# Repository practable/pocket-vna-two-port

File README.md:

# pocket-vna-two-port

A golang-based web service for the pocketvna.com](https://pocketvna.com/) vector network analyser, with an automated two-port calibration facility provided by additional RF hardware, for use with the open-source [practable.io](https://practable.io] remote lab ecosystem. The user interface is similar to [this](https://github.com/dpreid/pidui), although not yet publically released by the developer (coming soon!)

Status: Prototype has passed measurement quality check, and firmware has been updated to two-ports.

## API

Note that the optional "id" parameter does not affect the command itself, and is provided to help associate replies with the commands that produced them (in case responses come out of order)

### Reasonable range 

```
{"id":"rr","cmd":"rr"}
```
Response:
```
{"id":"rr","t":0,"cmd":"rr","range":{"start":500000,"end":4000000000}}
```

### Calibration

To Perform a full 2-port calibration issue a command like this:

```
{"id":"rcal","t":0,"cmd":"rc","range":{"start":1000000,"end":4000000000},"size":501,"islog":false,"avg":1}
```

501 points is quite slow, so for quick checking functionality, try fewer points.
```
{"id":"rcal","t":0,"cmd":"rc","range":{"start":1000000,"end":4000000000},"size":5,"islog":false,"avg":1}
```

 The `range`, `size`, `isLog` and `avg` are the same as before. This example uses the largest scan size possible (501 points)

### Measurement

These are all the measurements that can be taken (as before, they use the size, and range parameters from the cal):

```
{"id":"short","t":0,"cmd":"crq","what":"short","avg":1,"sparam":{"s11":true,"s12":true, "s21":true,"s22":true}}
{"id":"open","t":0,"cmd":"crq","what":"open","avg":1,"sparam":{"s11":true,"s12":true,"s21":true,"s22":true}}
{"id":"load","t":0,"cmd":"crq","what":"load","avg":1,"sparam":{"s11":true,"s12":true,"s21":true,"s22":true}}
{"id":"thru","t":0,"cmd":"crq","what":"thru","avg":1,"sparam":{"s11":true,"s12":true,"s21":true,"s22":true}}
{"id":"dut1","t":0,"cmd":"crq","what":"dut1","avg":1,"sparam":{"s11":true,"s12":true,"s21":true,"s22":true}}
{"id":"dut2","t":0,"cmd":"crq","what":"dut2","avg":1,"sparam":{"s11":true,"s12":true,"s21":true,"s22":true}}
{"id":"dut3","t":0,"cmd":"crq","what":"dut3","avg":1,"sparam":{"s11":true,"s12":true,"s21":true,"s22":true}}
{"id":"dut4","t":0,"cmd":"crq","what":"dut4","avg":1,"sparam":{"s11":true,"s12":true,"s21":true,"s22":true}} 
```

### Step wise calibration

New feature added to support students learning about the cal process

SC Command (Setup cal, sets the frequency range, number of points, distribution type, and averaging count)
`{"cmd":"sc","range":{"start":1000000,"end":4000000000},"size":20,"islog":false,"avg":1}`

SC Response
```
{"message":"ok","Command":{"id":"","t":0,"cmd":"sc","range":{"start":1000000,"end":4000000000},"size":20,"islog":false,"avg":1,"sparam":{"s11":false,"s12":false,"s21":false,"s22":false},"result":null,"what":"thru"}}
```

MC Short Command:
`{"cmd":"mc","what":"short"}`

MC Short Response (has no data):
```
{"message":"ok","Command":{"id":"","t":0,"cmd":"mc","range":{"start":0,"end":0},"size":0,"islog":false,"avg":0,"sparam":{"s11":false,"s12":false,"s21":false,"s22":false},"result":null,"what":"short"}}
```

MC Open Command:
`{"cmd":"mc","what":"open"}`

MC Open Response (has no data):
```
{"message":"ok","Command":{"id":"","t":0,"cmd":"mc","range":{"start":0,"end":0},"size":0,"islog":false,"avg":0,"sparam":{"s11":false,"s12":false,"s21":false,"s22":false},"result":null,"what":"open"}}
```

MC Load Command:
`{"cmd":"mc","what":"load"}`

MC Load Response (has no data):
```
{"message":"ok","Command":{"id":"","t":0,"cmd":"mc","range":{"start":0,"end":0},"size":0,"islog":false,"avg":0,"sparam":{"s11":false,"s12":false,"s21":false,"s22":false},"result":null,"what":"load"}}
```

MC Thru Command:

`{"cmd":"mc","what":"thru"}`

MC Thru Response (has no data):

```
{"message":"ok","Command":{"id":"","t":0,"cmd":"mc","range":{"start":0,"end":0},"size":0,"islog":false,"avg":0,"sparam":{"s11":false,"s12":false,"s21":false,"s22":false},"result":null,"what":"thru"}}
```

CC Command (cal confirm):

`{"cmd":"cc"}`

CC Command (has data, "what" indicates this is data for the thru with cal applied)
```
{"id":"","t":0,"cmd":"cc","range":{"start":0,"end":0},"size":0,"islog":false,"avg":0,"sparam":{"s11":false,"s12":false,"s21":false,"s22":false},"result":[{"s11":{"real":6.798285684431499e-16,"imag":2.4445757591977986e-15},"s12":{"real":1.0000000000000038,"imag":3.961372257700955e-15},"s21":{"real":0.9999999999999997,"imag":-2.5403542658420376e-15},"s22":{"real":-1.3100837207899224e-16,"imag":1.006857580582699e-15},"freq":1000000},{"s11":{"real":-5.4796192872464335e-18,"imag":3.681361022427108e-16},"s12":{"real":0.9999999999999998,"imag":1.291216167493111e-16},"s21":{"real":0.9999999999999998,"imag":1.0329729339944889e-16},"s22":{"real":-5.483483876630498e-16,"imag":2.274972688902102e-16},"freq":211473684},{"s11":{"real":4.935662660074536e-16,"imag":-7.96132869667085e-17},"s12":{"real":1.0000000000000002,"imag":9.417544964280893e-18},"s21":{"real":1,"imag":3.3389477600632256e-17},"s22":{"real":-5.493611090297354e-17,"imag":2.7110250401774997e-17},"freq":421947368},{"s11":{"real":-3.7997788415861466e-16,"imag":-5.874815142871674e-16},"s12":{"real":0.9999999999999998,"imag":-1.3589387524604561e-17},"s21":{"real":1,"imag":1.358938752460456e-16},"s22":{"real":2.7701351888980784e-16,"imag":2.4761558453947516e-16},"freq":632421052},{"s11":{"real":-1.770339245638541e-16,"imag":1.9778244425109326e-16},"s12":{"real":1,"imag":-8.300789127383292e-17},"s21":{"real":1,"imag":-1.3834648545638821e-17},"s22":{"real":1.8971165707760076e-16,"imag":2.4057070110192795e-16},"freq":842894736},{"s11":{"real":-4.2721621505142654e-16,"imag":-3.6944203527273236e-16},"s12":{"real":1.0000000000000002,"imag":1.0316557900882054e-16},"s21":{"real":1,"imag":2.3212255276984624e-16},"s22":{"real":1.4673180020770904e-16,"imag":-7.563249442097559e-17},"freq":1053368421},{"s11":{"real":-7.434581424175234e-17,"imag":-1.9738283167151276e-16},"s12":{"real":1.0000000000000007,"imag":2.653377447265651e-16},"s21":{"real":1,"imag":1.3668914122277596e-16},"s22":{"real":-2.3401087672749595e-16,"imag":1.0842732839585657e-15},"freq":1263842105},{"s11":{"real":3.6225925572304583e-16,"imag":-6.553331226630913e-16},"s12":{"real":1.0000000000000002,"imag":-7.697793525240971e-18},"s21":{"real":1,"imag":-2.232360122319882e-16},"s22":{"real":-1.664758573382055e-16,"imag":4.426697324102885e-16},"freq":1474315789},{"s11":{"real":-2.1111596138986894e-16,"imag":-3.374000478864848e-16},"s12":{"real":0.9999999999999998,"imag":2.500148396700068e-16},"s21":{"real":0.9999999999999997,"imag":1.388971331500038e-16},"s22":{"real":-9.217893404457907e-16,"imag":5.883978158950974e-16},"freq":1684789473},{"s11":{"real":-9.143566579079719e-17,"imag":-1.211669953147277e-16},"s12":{"real":0.9999999999999994,"imag":-3.384880863400854e-16},"s21":{"real":0.9999999999999997,"imag":-1.9131935314874394e-16},"s22":{"real":7.370339974993562e-16,"imag":-8.28234587808332e-16},"freq":1895263157},{"s11":{"real":6.457509151560786e-16,"imag":3.8407024419460014e-16},"s12":{"real":1,"imag":1.9729520543081967e-16},"s21":{"real":1,"imag":1.1097855305483607e-16},"s22":{"real":6.60122631708177e-16,"imag":1.3745123740607558e-16},"freq":2105736842},{"s11":{"real":-3.3440705904509994e-17,"imag":4.449237964595957e-17},"s12":{"real":1.0000000000000002,"imag":-2.5977695183489855e-17},"s21":{"real":1,"imag":-2.5977695183489855e-17},"s22":{"real":-5.030390119684563e-17,"imag":2.0588438761762348e-16},"freq":2316210526},{"s11":{"real":9.761453389683951e-16,"imag":9.948440742403095e-16},"s12":{"real":1,"imag":3.198724411505024e-18},"s21":{"real":1,"imag":-6.173538114204697e-16},"s22":{"real":-5.60392729997236e-16,"imag":1.011513121527802e-15},"freq":2526684210},{"s11":{"real":3.4281792534273156e-16,"imag":1.8971075667988323e-16},"s12":{"real":0.9999999999999998,"imag":1.1750683925917896e-16},"s21":{"real":1.0000000000000002,"imag":-4.0090568688425766e-16},"s22":{"real":-4.803256717402525e-16,"imag":-1.6853048357543685e-16},"freq":2737157894},{"s11":{"real":7.0222190594856e-16,"imag":8.55812317471566e-16},"s12":{"real":0.9999999999999988,"imag":-1.1169563182435168e-15},"s21":{"real":0.9999999999999999,"imag":9.307969318695973e-17},"s22":{"real":1.2657248559624003e-15,"imag":-4.1238155967451286e-16},"freq":2947631578},{"s11":{"real":3.858821128617499e-16,"imag":-5.908283352150228e-16},"s12":{"real":1.0000000000000004,"imag":2.7559016913199073e-16},"s21":{"real":0.9999999999999999,"imag":-3.1910440636335773e-16},"s22":{"real":-8.995649578270255e-16,"imag":1.3676784350870345e-15},"freq":3158105263},{"s11":{"real":2.1930623628836212e-15,"imag":-4.471183287954572e-16},"s12":{"real":1.0000000000000007,"imag":6.624851261896299e-17},"s21":{"real":1.0000000000000009,"imag":-1.5568400465456302e-15},"s22":{"real":-3.910813152158192e-16,"imag":1.497689622024306e-16},"freq":3368578947},{"s11":{"real":-2.146668654496036e-15,"imag":-1.183624872561583e-15},"s12":{"real":1.0000000000000009,"imag":8.946818283441143e-16},"s21":{"real":0.9999999999999997,"imag":7.437272811749428e-16},"s22":{"real":-7.642394840158961e-16,"imag":1.3994328139316487e-15},"freq":3579052631},{"s11":{"real":2.7529090287958957e-17,"imag":7.844753059553777e-16},"s12":{"real":1.0000000000000007,"imag":4.241877296255027e-16},"s21":{"real":1.0000000000000007,"imag":-1.4812904844065175e-16},"s22":{"real":1.4749059628833424e-17,"imag":7.703227823525666e-16},"freq":3789526315},{"s11":{"real":2.1613952847620654e-15,"imag":-1.4106120953151985e-15},"s12":{"real":1.0000000000000018,"imag":1.8138127619939417e-16},"s21":{"real":0.9999999999999996,"imag":-5.654828022686995e-16},"s22":{"real":8.233651548249787e-16,"imag":1.6094852797772485e-15},"freq":4000000000}],"what":"thru"}
```

 If you try to confirm the cal or take a measurement before completing the cal, then you will get an error message, e.g. sending cc before doing anything else ...
 
```
{"message":"not calibrated yet","Command":{"id":"","t":0,"cmd":"cc","range":{"start":0,"end":0},"size":0,"islog":false,"avg":0,"sparam":{"s11":false,"s12":false,"s21":false,"s22":false},"result":null,"what":""}}
```

 If you have started but not finished the cal, then there will be a hint about what is missing. It's not very sophisticated, it checks for short, open, load thru in that order but it is ok to do the measurements in any order. E.g. if you have only done the `sc` and then `mc` for the `short`, and then try `cc`, you get
```
{"message":"calibration not complete (missing open, maybe others)","Command":{"id":"","t":0,"cmd":"cc","range":{"start":0,"end":0},"size":0,"islog":false,"avg":0,"sparam":{"s11":false,"s12":false,"s21":false,"s22":false},"result":null,"what":""}}
```
But if you try a crq, you don't; get any hints, just a message it is not calibrated yet:

CRQ command

```
{"id":"short","t":0,"cmd":"crq","what":"short","avg":1,"sparam":{"s11":true,"s12":true, "s21":true,"s22":true}}
```

CRQ response

```
{"message":"not calibrated yet","Command":{"id":"short","t":0,"cmd":"crq","what":"short","avg":1,"sparam":{"s11":true,"s12":true,"s21":true,"s22":true},"result":null}}
```

### Trying it out

use the dev-debug because it has been modified to display the data stream more conveniently

request rr:
```
{"id":"rr","t":0,"cmd":"rr","range":{"start":500000,"end":4000000000}}
```
response
```
{"id":"rcal","t":0,"cmd":"rc","range":{"start":1000000,"end":4000000000},"size":501,"islog":false,"avg":1}
```

request cal
```
{"id":"rcal","t":0,"cmd":"rc","range":{"start":1000000,"end":4000000000},"size":3,"islog":false,"avg":1}
```
response
```
{"id":"rcal","t":0,"cmd":"rc","range":{"start":1000000,"end":4000000000},"size":3,"islog":false,"avg":1,"sparam":{"s11":false,"s12":false,"s21":false,"s22":false},"result":[{"s11":{"real":-0.00002794712781906128,"imag":-0.0002553611993789673},"s12":{"real":0.00004700571298599243,"imag":0.000007621943950653076},"s21":{"real":0.00005336105823516846,"imag":-0.000005081295967102051},"s22":{"real":0.000048279762268066406,"imag":-0.00021597743034362793},"freq":1000000},{"s11":{"real":-0.0000025406479835510254,"imag":-0.0002896711230278015},"s12":{"real":0.0015550479292869568,"imag":-0.00180024653673172},"s21":{"real":-0.0020975321531295776,"imag":0.001013830304145813},"s22":{"real":-0.0018929839134216309,"imag":0.0009096488356590271},"freq":2000500000},{"s11":{"real":0.002163603901863098,"imag":-0.008152559399604797},"s12":{"real":0.0015474259853363037,"imag":-0.0013009533286094666},"s21":{"real":0.0024291202425956726,"imag":0.0006962120532989502},"s22":{"real":0.0027683377265930176,"imag":-0.006796970963478088},"freq":4000000000}],"what":""}
```

request measurement
```
{"id":"dut1","t":0,"cmd":"crq","what":"dut1","avg":1,"sparam":{"s11":true,"s12":true,"s21":true,"s22":true}}
```
response
```
{"id":"dut1","t":0,"cmd":"crq","what":"dut1","avg":1,"sparam":{"s11":true,"s12":true,"s21":true,"s22":true},"result":[{"s11":{"real":0.7213804056329582,"imag":1.4104697588145223},"s12":{"real":-0.6894871206139953,"imag":0.2700840697023531},"s21":{"real":0.7031091027298517,"imag":0.47775336746611247},"s22":{"real":0.10341030075671172,"imag":0.3654223580872504},"freq":1000000},{"s11":{"real":-0.21755274620868625,"imag":-0.3754279747150785},"s12":{"real":0.6896210346136951,"imag":-0.12124783800081158},"s21":{"real":0.5913287788642378,"imag":-0.17444370058172678},"s22":{"real":-0.19807969221279273,"imag":-0.3255108569280837},"freq":2000500000},{"s11":{"real":-0.6383708479867005,"imag":-0.14863376649864046},"s12":{"real":0.29690952420750577,"imag":-0.0448141195835949},"s21":{"real":0.32891032123190567,"imag":0.003536763868706301},"s22":{"real":-0.4513970279816097,"imag":-0.14868940500662153},"freq":4000000000}]}
```

## Two port set up

## Pin connections

| Pin | Connection      |
|-----|-----------------|
| 2   | Switch Power    |
| 3   | Switch Power    |
| 4   | Port 2 Switch A |
| 5   | Port 2 Switch B |
| 6   | Port 2 Switch C |
| 8   | Port 1 Switch A |
| 9   | Port 1 Switch B |
| 10  | Port 1 Switch C |
| 15  | Port 2 LED      |
| 16  | Port 1 LED      |

## Switch Configuration

The states available in the prototype firmware were:

| State       | P1-A (D8) | P1-B (D9) | P1-C (D10) | P2-A (D4) | P2-B (D5) | P2-C (D6) |
|-------------|-----------|-----------|------------|-----------|-----------|-----------|
| P1 Short    | 0         | 0         | 1          | X         | X         | X         |
| P1 Open     | 0         | 1         | 0          | X         | X         | X         |
| P1 Load     | 0         | 1         | 1          | X         | X         | X         |
| P2 Short    | X         | X         | X          | 1         | 0         | 0         |
| P2 Open     | X         | X         | X          | 1         | 0         | 1         |
| P2 Load     | X         | X         | X          | 1         | 1         | 0         |
| Thru        | 1         | 0         | 0          | 0         | 1         | 1         |
| DUT-1 (5-2) | 1         | 0         | 1          | 0         | 1         | 0         |
| Ch0 P2      | X         | X         | X          | 0         | 0         | 0         |
| Ch1 P2      | X         | X         | X          | 0         | 0         | 1         |
| Ch7 P2      | X         | X         | X          | 1         | 1         | 1         |
| Ch0 P1      | 0         | 0         | 0          | X         | X         | X         |
| Ch6 P1      | 1         | 1         | 0          | X         | X         | X         |
| Ch7 P1      | 1         | 1         | 1          | X         | X         | X         |
| DUT-2 (6-1) | 1         | 1         | 0          | 0         | 0         | 1         |
| DUT-3 (7-0) | 1         | 1         | 1          | 0         | 0         | 0         |
| DUT-4 (0-7) | 0         | 0         | 0          | 1         | 1         | 1         |

The revised, minimal states are:

| State       | P1-A (D8) | P1-B (D9) | P1-C (D10) | P2-A (D4) | P2-B (D5) | P2-C (D6) |
|-------------|-----------|-----------|------------|-----------|-----------|-----------|
| P1 Short    | 0         | 0         | 1          | X         | X         | X         |
| P1 Open     | 0         | 1         | 0          | X         | X         | X         |
| P1 Load     | 0         | 1         | 1          | X         | X         | X         |
| P2 Short    | X         | X         | X          | 1         | 0         | 0         |
| P2 Open     | X         | X         | X          | 1         | 0         | 1         |
| P2 Load     | X         | X         | X          | 1         | 1         | 0         |
| Thru        | 1         | 0         | 0          | 0         | 1         | 1         |
| DUT-1       | 1         | 0         | 1          | 0         | 1         | 0         |
| DUT-2       | 1         | 1         | 0          | 0         | 0         | 1         |
| DUT-3       | 1         | 1         | 1          | 0         | 0         | 0         |
| DUT-4       | 0         | 0         | 0          | 1         | 1         | 1         |

Or in decimal

| State       | P1        | P2        | 
|-------------|-----------|-----------|
| Short       | 1         | 4         |
| Open        | 2         | 5         |
| Load        | 3         | 6         |
| Thru        | 4         | 3         |
| DUT-1       | 5         | 2         |
| DUT-2       | 6         | 1         |
| DUT-3       | 7         | 0         |
| DUT-4       | 0         | 7         |

This table implies the following connections:

### Port 1

| Channel   | Connection |
|-----------|------------|
| RF1       | DUT-4      |
| RF2       | Short      |
| RF3       | Open       |
| RF4       | Load       |
| RF5       | Thru       |
| RF6       | DUT-1      |
| RF7       | DUT-2      |
| RF8       | DUT-3      |

### Port 2

| Channel   | Connection |
|-----------|------------|
| RF1       | DUT-3      |
| RF2       | DUT-2      |
| RF3       | DUT-1      |
| RF4       | Thru       |
| RF5       | Short      |
| RF6       | Open       |
| RF7       | Load       |
| RF8       | DUT-4      |

These connections tally with the prototype.

Note that the connection on the HM321 RF chip on the datasheet.

### Current DUT Setup

The prototype as at 2023-03-02 is set up as follows:

| DUT | Type           | Port/Switch 1 | Port/Switch 2 | 
|-----|----------------|---------------|---------------|
| 1   | 2-Port Filter  | P1            | P2            |
| 2   | 4-Port Coupler | P1            | P4            | 
| 3   | 4-Port Coupler | P1            | P2            |
| 4   | 4-Port Coupler | P1            | P3            |

The 4-Port couplers are all the same, but with different port connections, to allow all four ports to be measured (albeit not as completely as a four-port VNA).

## Current results

Set debug=true to get a table showing the outputs

```
        P1      P2     P1  P2
short: 1 0 0   0 0 1   1   4
open : 0 1 0   1 0 1   2   5
load : 1 1 0   0 1 1   3   6
thru : 0 0 1   1 1 0   4   3
dut1 : 1 0 1   0 1 0   5   2
dut2 : 0 1 1   1 0 0   6   1
dut3 : 1 1 1   0 0 0   7   0
dut4 : 0 0 0   1 1 1   0   7
```

## Developers

This section contains notes for developers. The code was refactored during 2023 to account for a bug that required two measurements to be taken in a row before the correct DUT was measured. 

### Measurements

A typical user request is for a calibrated measurement of a particular device under test (DUT).

 The `pkg/middle` receives that request over a websocket connection implemented by `pkg/stream`. Upon startup, the firmware makes a local connection to a `relay host` that is in turn connected to the `relay server` instance running in the cloud, that is turn connected to the user.

`pkg/middle` must take a number of measurements, both of cal standards and the DUT, then request a calibration calculation. Measurements require the RF switch to be set to connect the VNA to the right DUT or cal standard.

The `pkg/measure` package combines an RF switch (`pkg/rfusb`) and VNA instance (`pkg/pocket`) together so that it is straightforward to request a particular measurement. 

Once all the required measurements are taken (SOLT + DUT), then using the method shown in `pkg/calibrate`, the gRPC client in `pkjg/pb` is used to request the calibration from our local calibration server - see `py/server.py`. This needs to run locally to the firware because gRPC is HTTP/2 and that is not proxied by the cloud frontends available to us at present. The code in `pkg/pb` is autogenerated protocol buffer code.

```mermaid
 erDiagram
    USER }o--o{ CALIBRATED_MEASUREMENT : requests
    CALIBRATED_MEASUREMENT {
        string port
        array frequencyRange
        result  CalibratedSParametersDUT
    }
    CALIBRATED_MEASUREMENT ||--|| CALIBRATION : requires
        CALIBRATION {
            SParameters short
            SParameters open
            SParameters load
            SParameters thru
            SParameters DUT

        }
     CALIBRATION ||--|{ MEASUREMENT : requires
        MEASUREMENT {
                 string port
        }
    MEASUREMENT ||--|| HARDWARE : requires
        HARDWARE{
        pointer switch
            pointer VNA
        }    
```

TODO 

0. `middle` update hardware test to cycle through all dut at least twice, and then a third time in a different order
1. `middle` Use new direct switch connection in middle
2. `middle` Use new grpc connection in middle

### Golang files

The golang packages are in `./pkg`

If adding new subpackages, then update the reference to the project to the current branch, e.g. after adding the package `pb` to the `fix` branch, `go mod` couldn't find it `@latest` so it needed to be "upgraded" to look at the fix branch. Warning - after pulling to main, update to point to @latest again
```
go get -v -u github.com/practable/pocket-vna-two-port/pkg/pb@fix
go mod tidy
```
### Architecture

The RF Switch is connected directly rather than via `socat`+`websocat` as in the previous generation. This simplifies the configuration of the single board computer and avoids switch commands getting out of sequence on a channel.

The calibration is via gRPC call, again to avoid responses getting out of sequence over a channel. Note that gRPC uses HTTP/2 so we are probably stuck with running this locally on a container

### Building

### Testing

## Overview from the one-port repo

These notes should aid in understanding the ansible scripts in `./sbc`, even though some details differ. Note that the below information has NOT been edited to match changes in the current repo, so differs in the detail e.g. of calibration commands (now two-port), and S-parameter settings in the measurement commands. See commands above for the current version.

This repo contains code and design files for the key parts of the system.

- golang wrapper for the pocket-vna
- golang middleware and clients for the rf-switch and calibration services 
- python calibration service using scikit-rf & websocket libraries
- docker containerisation of the python calibration service
- C/C++ firmware for an arduino nano microcontroller
-
The largest part of this repo is the golang executable `vna` which sequences tasks between the four major parts: 
- user (via websocket service, routed through session host from the external practable.io ecosystem)
- vector network analyser (via golang-wrapped shared C library; local USB connection to hardware)
- rf switch controller (via websocket service, routed through session host; local USB connection to hardware)
- calibration service (via websocket service, routed through session host; runs on local docker container)

`vna` also supplies a `unlock` command to free up any pocketVNA connected to the computer. It is assumed that you only have one VNA per computer (it's possible to support more, and to choose explicitly, but that is not implemented. Our use case is one VNA per host computer,  and we want to auto-discover the VNA).

For example, in order to perform a calibration, the golang code does the following tasks

- set the RF switch to the short cal standard
- scan the short, and store the data
- set the RF switch to the open cal standard
- scan the open, and store the data
- set the RF switch to the load cal standard
- scan the load, and store the data
- check all the data are of the correct length

To supply calibrated scans, the golang code does the following

- set the RF switch to the device under test (or whichever cal standard the user is interested in scanning)
- scan the device under test with the same parameters for which we have cal-standard data
- combine the dut data with the cal standard data, and send to the calibration service
- receive the results, re-format the data, and send it to the user

There is a <100ms performance overhead in sending the cal data to the calibration service each time, but this is much smaller than the scan times (tens of seconds), and avoids duplicating state (such as knowledge of what frequency points are being used, and when the cal standards were last scanned).

## Future expansion

Our preferred languages for each of the different parts of the system spanned golang, C/C++ and python. Instead of trying to tightly integrate them or duplicate functionality in one or the other, the JSON-over-websockets communication method was used to separate out concerns, facilitate testing, and allow replacing the RF switch circuit to support two-port cal, add extra calibration methods, and upgrade the API offered to the user to support the extra hardware.

## Installation 

This can be a bit finicky because the pocketVNA library has different name and requirements for different targets, and is only available as compiled source so cannot be automatically built for your target. The manufacturers support a number of major operating systems and platforms, so you should be ok. This code has been tested on amd64/linux and arm/linux.

### vna install 

The core of this repo is the `vna` executable.

0. Download this repo (`git clone git@github.com:timdrysdale/go-pocketvna.git`)
0. replace pkg/pocket/libPocketAPI.so with the appropriate pocketVNA library for your target
0. copy that library to your system path, e.g. for linux /usr/lib (for linux amd64/arm, add `.0` so the ending is `...so.0`)
0. get all dependencies `go get -u ./...' (you may need to add or remove the -lm flag for linking the maths library - not needed on linux 64 bit but needed on Raspbian buster
0. Compile the vna command (`go mod init github.com/timdrysdale/go-pocketvna && cd cmd/vna && go build`)
0. copy the `vna` executable to your usual location on the path (`go install` or do by hand)
0. check it is installed by trying `vna stream --help`

```
vna stream --help
Stream connects the first available pocketVNA to a websocket server. The websocket server is specified via an environment variable

export VNA_DESTINATION=ws://localhost:8888/ws/vna
export VNA_CALIBRATION=ws://localhost:8888/ws/calibration
export VNA_RFSWITCH=ws://localhost:8888/ws/rfswitch

vna stream 

Note that development can be enabled by setting environment variable VNA_DEVELOPMENT
export VNA_DEVELOPMENT=true

Usage:
  vna stream [flags]

Flags:
  -h, --help   help for stream
```

### session install

Install `session` from [practable.io](https://github.com/practable/relay)

If you are using the experiment remotely, you should configure a script to set the forwarding rules at start up (your practable.io admin contact will have details of the tokens etc your experiment needs)

session-rules
```
#!/bin/sh
dataTokenFile="/etc/practable/data.token"
dataAccessFile="/etc/practable/data.access"

dataToken=$(cat "$dataTokenFile")
dataAccess=$(cat "$dataAccessFile")

curl -X POST -H "Content-Type: application/json" -d '{"stream":"data","destination":"'"${dataAccess}"'","id":"1","token":"'"${dataToken}"'"}' http://localhost:8888/api/destinations 
```
This script can be run at start up by enabling a systemd service. The service file is in [services](./ansible/services)

### Docker install

Python is often used for system tasks, so we run our calibration service in a docker container to avoid any version and dependency conflicts.

The steps to manually install Docker are:

```
sudo apt update
# optional:
# sudo apt-upgrade && sudo reboot
curl -fsSL https://get.docker.com -o get-docker.sh
chmod +x ./get-docker.sh
sudo ./get-docker.sh

# for non-privileged use
dockerd-rootless-setuptool.sh install
#check you have docker running
docker version 
#sudo usermod -aG docker $(whoami) #this not be needed -
sudo chmod 666 /var/run/docker.sock #avoid permission denied
#sudo reboot #let all the changes take effect
#<wait for reboot>
```

Build and start the docker image (use tmux if you are ssh'ing into your rpi, so you can have extra terminals open)
```
export platform=linux-amd64  #or linux-arm32v7
cd py/docker/app-${platform}
./build.sh && ./start.sh
```

You can check the calibration service is up and running by connecting to it with `websocat`

```
$ websocat ws://localhost:8888/ws/calibration -
```

Calibration commands are usually quite long, so here is one with just a single data point
```
{"cmd": "oneport", "freq": [1000000.0], "short": {"real": [0.9166423490437918], "imag": [0.65760561459272446]}, "open": {"real": [0.8574903206586918], "imag": [0.43502949254752743]}, "load": {"real": [0.3002840906307519], "imag": [0.297151596182326]}, "dut": {"real": [0.4975782258013943], "imag": [0.4293572766329692]}}
```
which will return a response like this:

```
{"freq": [1000000.0], "S11": {"Real": 0.032134147957021554, "Imag": 0.0984021118681623}}
```

## vna setup
 
The usage / setup is mostly the same for a local system running on a desktop for testing, or deployed on a raspberry pi for remote access. The remote system tends to have everything autostart on boot, and include some setup to make a connection to the `practable.io` infrastructure servers. This is added complication that you do not need, and may not want, if working on a desktop. Starting the services manually is fine. Start `session host` first, then `websocat`, then you can start `socat`, `vna stream` and the `docker` calibration service in any order. The system will only supply calibrated data when the rfswitch and calibration services are running.

It is recommended to try unlocking the devices first - just in case the service is restarting and the pocketVNA was locked by the previous instance

The websocket connections between services are specified by environment variables, so that `vna stream` knows where to find them. The `session host` does not mind which particular endpoints are used - but the endpoints must be set the same for `vna stream` and the service that it is connecting to. The full instantiation of the [practable.io](https://practable.io) services on the host computer (usually a raspberry pi) are out of the scope of this documentation (early adopters are encouraged to contact us for information on how to obtain support <support@practable.io>).

Assuming your target is already running [relay/sessionhost](https://github.com/timdrysdale/relay) (see `cmd/session`), then you can use the following files to automate the startup of the services you need:

vna-data:
```
#!/bin/bash
export VNA_DESTINATION=ws://localhost:8888/ws/data
export VNA_CALIBRATION=ws://localhost:8888/ws/calibration
export VNA_RFSWITCH=ws://localhost:8888/ws/rfswitch
vna unlock
vna stream
```

socat-rfswitch:
```
#!/bin/sh
socat /dev/ttyUSB0,echo=0,b57600,crnl tcp:127.0.0.1:9999
```

Note you may have to add yourself to the dialout and tty groups.
```
sudo usermod -a -G dialout pi
sudo usermod -a -G tty pi
```

websocat-rfswitch:
```
#!/bin/sh
websocat ws://localhost:8888/ws/rfswitch tcp-listen:127.0.0.1:9999 --text
```

You can check the `rfswitch` is running by 
```
websocat ws://localhost:8888/ws/rfswitch -
```
Issue commands to change the port
```
{"set":"port","to":"open"}
```

should yield a reply of
```
{"report":"port","is":"open"}
```

### Service files

Service files are in <./ansible/services>. Note most are fairly similar, except `socat-data` which must wait long enough that `websocat-data` has started (ca 10s leaves a safe margin in practice).

### Verifying that the services are working

Connect to `vna` over websocket using `websocat`
```
websocat ws://localhost:8888/ws/data -
```
Then send a ReasonableFrequencyRange command
```
{"cmd":"rr"}
```
which should return something like
```
{"id":"","t":0,"cmd":"rr","range":{"start":500000,"end":4000000000}}
```

This confirms that `vna` is up and running, and connected to a pocketVNA.

Now try a command that needs the rfswitch
```
{"cmd":"rc","range":{"start":1000000,"end":4000000000},"size":3,"islog":false,"avg":1,"sparam":{"s11":true,"s12":false,"s21":false,"s22":false}}
```
should return something like:

```
{"id":"","t":0,"cmd":"rc","range":{"start":1000000,"end":4000000000},"size":3,"islog":false,"avg":1,"sparam":{"s11":true,"s12":false,"s21":false,"s22":false},"result":[{"s11":{"real":-0.0007592514157295227,"imag":0.0006944984197616577},"s12":{"real":0,"imag":0},"s21":{"real":0,"imag":0},"s22":{"real":0,"imag":0},"freq":1000000},{"s11":{"real":0.0004634261131286621,"imag":-0.0001447424292564392},"s12":{"real":0,"imag":0},"s21":{"real":0,"imag":0},"s22":{"real":0,"imag":0},"freq":2000500000},{"s11":{"real":0.0024859830737113953,"imag":-0.005337625741958618},"s12":{"real":0,"imag":0},"s21":{"real":0,"imag":0},"s22":{"real":0,"imag":0},"freq":4000000000}]}

```

and a command that needs the calibration service

```
{"cmd":"crq","what":"dut","avg":1,"sparam":{"s11":true,"s12":false,"s21":false,"s22":false}}
```

which should return something like:

```
{"id":"","t":0,"cmd":"crq","what":"dut","avg":1,"sparam":{"s11":true,"s12":false,"s21":false,"s22":false},"result":[{"s11":{"real":1.0031062693348898,"imag":-0.012728241016514735},"s12":{"real":0,"imag":0},"s21":{"real":0,"imag":0},"s22":{"real":0,"imag":0},"freq":1000000},{"s11":{"real":-0.1335237960932827,"imag":-0.09618931729902436},"s12":{"real":0,"imag":0},"s21":{"real":0,"imag":0},"s22":{"real":0,"imag":0},"freq":2000500000},{"s11":{"real":-0.4883905666762738,"imag":-0.13897086282584725},"s12":{"real":0,"imag":0},"s21":{"real":0,"imag":0},"s22":{"real":0,"imag":0},"freq":4000000000}]}
```

## Interface 

There are three commands directly supported by the pocketvna shared library:

0. `rr`: get the reasonable frequency range for the device (useful `proof of connection` command when troubleshooting)
0. `sq`: get S-parameters at a single frequency (uncalibrated)
0. `rq`: get S-paramters at a range of frequencies (uncalibrated)

we add two more commands to support calibration, which are the two main commands we use: 

0. `rc`: do a calibration over a frequency range for a certain number of steps 

0. `crq`: get S-parameters frequencies (calibrated), using whatever frequency points were specified in the last `rc`

There is also a heartbeat sent every second from the driver, to let you know it is still connected. You can use the absence of this heartbeat to infer that your connection has dropped (it is unlikely the driver has stopped, although that is technically possible if there is a power outage). This heartbeat is added because VNA experiments are unlikely to use a camera (and we've been using the video to check for connection drops, so without it we need something else to check).

```
{"cmd":"hb"}
```

In order to relate commands to responses you can include an ID `id` (string) and/or time `t` (int) field.

### rr

Command

```
{"cmd":"rr"}
```

Response

```
{"id":"","t":0,"cmd":"rr","range":{"Start":500000,"End":4000000000}}
```

Start is the lowest frequency (in Hz) that the VNA can operate at, and End is the highest.

### sq

`sq` gets the requested S-parameters at a single frequency. 

The parameters are:

    - freq (in Hz) at which to take the measurement at
	- avg number of times to take the reading (which are then averaged together)
	- sparam select which S-params are needed - the more you select, the longer it takes

Command:

```
{"id":"945102d5-94e4-448e-bbbf-48384c662711","t":1634664795,"cmd":"sq","freq":100000,"avg":1,"sparam":{"S11":true,"S12":false,"S21":true,"S22":false}}
```
Response:

```
{"id":"945102d5-94e4-448e-bbbf-48384c662711","t":1634664795,"cmd":"sq","freq":100000,"avg":1,"sparam":{"S11":true,"S12":false,"S21":true,"S22":false},"result":{"S11":{"Real":0.0001702234148979187,"Imag":0.0005754455924034119},"S12":{"Real":0,"Imag":0},"S21":{"Real":-0.00004191696643829346,"Imag":-0.00012067705392837524},"S22":{"Real":0,"Imag":0}}}
```

### rq

Get the requested S-parameters at a range of frequencies. Parameters:

    - range (start, end) the start and end of the frequency range to take measurements
	- size the number of separate frequency points to measure at, across the range
	- isLog whether to use a log (isLog = true) or linear (isLog = false) distribution
	- avg number of times to take each reading (which are then averaged together)
	- sparam select which S-params are needed - the more you select, the longer it takes

command
```
{"cmd":"rq","range":{"Start":100000,"End":4000000},"size":2,"isLog":true,"avg":1,"sparam":{"S11":true,"S12":false,"S21":true,"S22":false}}
```

response
```
{"id":"","t":0,"cmd":"rq","range":{"Start":100000,"End":4000000},"size":2,"isLog":true,"avg":1,"sparam":{"S11":true,"S12":false,"S21":true,"S22":false},"result":[{"S11":{"Real":0.00013846158981323242,"Imag":0.00027057528495788574},"S12":{"Real":0,"Imag":0},"S21":{"Real":-0.000031754374504089355,"Imag":-0.0002350062131881714},"S22":{"Real":0,"Imag":0}},{"S11":{"Real":0.00470772385597229,"Imag":0.003948085010051727},"S12":{"Real":0,"Imag":0},"S21":{"Real":0.000017777085304260254,"Imag":-0.000005081295967102051},"S22":{"Real":0,"Imag":0}}]}
```

Note that the frequencies are not (currently) included in the response. They can be calculated according to the formulas given in the openAPI library header, which are (@p denotes a parameter, e.g. ```@p start``` means the parameter start)

```
     *  Distributions:
     *    Linear:      (@p start * 1000 + ((@p end - @p start) * 1000 / (@p steps - 1)) * index) / 1000
     *       (Pay Attention: all numbers are integers. Last element is forced to be equalt to @p end)
     *    Logarithmic: (@p from * powf((float)to / from, (float)index / (steps - 1)))
     *       Formula is taken from 10 ** (lg from +  ( lg to - lg from ) * index /  (steps - 1)). 4-bytes float are used
     *       Pay attention: arithmetic is pretty imprecise on a device
	 
```
These frequency points are calculated in this library, because they are not sent from the hardware. Here is a table of 11 points from 1MHz - 500MHz, taken from the native application for Linear and Log scans. Note that these values from the native app are not quite the same as we expect from the formula for the case of a Log distribution, although the precision issue is acknowledged in the library header file from the supplier as if it is a hardware issue but the values are probably calculated in the native app - the differences are quite small and probably not significant.

| Point  | Linear (both)     |  Log (native app)      | Log (go-pocketVNA)      |  delta |
| -------|-------------|------------|-----------|--------|
| 0      |  1000000    | 1000000    | 1000000   |        |
| 1      |  50900000   | 1861646    | 1861646   |        |
| 2      |  100800000  | 3465724    | 3465724   |        |
| 3      |  150700000  | 6451951    | 6451950   |  -1    |
| 4      |  200600000  | 12011245   | 12011244  |  -1    |
| 5      |  250500000  | 22360680   | 22360680  |        |
| 6      |  300400000  | 41627668   | 41627660  |  -8    |
| 7      |  350300000  | 77495944   | 77495949  |  +5    |
| 8      |  400200000  | 144270000  | 144269991 |  -9    |
| 9      |  450100000  | 268579552  | 268579588 | +36    |
| 11     |  500000000  | 500000000  | 500000000 |        |

### rc

This uses the same JSON structure as the `rq` command, but change `"cmd":"rq"` to `"cmd":"rc"` and ensure that `"sparam":{"S11":true,"S12":false,"S21":false,"S22":false}}` because only cal on port one is supported:

```
{"cmd":"rc","range":{"Start":100000,"End":4000000},"size":2,"isLog":true,"avg":1,"sparam":{"S11":true,"S12":false,"S21":false,"S22":false}}
```

The maximum size is 512, and it is conventional to ask for 501 points for a nice even spacing. A calibration for 501 points takes approx 30 seconds.

### crq

This is a subset of the `rq` object, with `"cmd":"crq"`, and ensure that `"sparam":{"S11":true,"S12":false,"S21":false,"S22":false}}`

```
{"cmd":"crq","avg":1,"sparam":{"S11":true,"S12":false,"S21":false,"S22":false}}
```

## Example data

Good data from a passive device under test always returns a gain of less than 0dB (i.e. without power from a bias supply, it can't add any power of its own) so we can see that in the following results, we should not rely on values close to DC (for the calibration we did, at least). Also, there is some drift in this measurement of a cable, bearing in mind the cable was re-connected after the first few scans and the device moved, so not an entirely fair test on the device. This data was collected in the native app and plotted using python's matplotlib.pyplot.

### Raw data 

```
{"cmd":"rq","range":{"Start":100000,"End":4000000},"size":201,"isLog":true,"avg":1,"sparam":{"S11":true,"S12":true,"S21":true,"S22":true}}
```

Result returns about 15 sec later, with S-parameters at 201 frequency points:

```
{"id":"","t":0,"cmd":"rq","range":{"Start":100000,"End":4000000},"size":201,"isLog":true,"avg":1,"sparam":{"S11":true,"S12":true,"S21":true,"S22":true},"result":[{"S11":{"Real":0.000034302473068237305,"Imag":0.00037600845098495483},"S12":{"Real":-0.0010073482990264893,"Imag":0.00012448430061340332},"S21":{"Real":-0.0013414323329925537,"Imag":0.0005551204085350037},"S22":{"Real":0.00003937631845474243,"Imag":0.00023628026247024536},"Freq":100000},{"S11":{"Real":0.00006987154483795166,"Imag":0.00010670721530914307},"S12":{"Real":-0.0010479986667633057,"Imag":0.00009654462337493896},"S21":{"Real":-0.0013172999024391174,"Imag":0.0008002892136573792},"S22":{"Real":0.00007876008749008179,"Imag":0.0003162994980812073},"Freq":101862},{"S11":{"Real":0.00014227628707885742,"Imag":0.00035568326711654663},"S12":{"Real":-0.0010594278573989868,"Imag":0.0003429800271987915},"S21":{"Real":-0.0013439729809761047,"Imag":0.0009235069155693054},"S22":{"Real":0.00011432915925979614,"Imag":0.0001664087176322937},"Freq":103758}, ... <snip> ...]}
```

## Developer info

These sections contain some information that may be relevant to developers.

### CGO info

An example of using cgo can be found [here](https://github.com/timhughes/cgoexample) - note you have to delete hello.c from the project directory to avoid `multiple definition of main` error.

There are some differences between C and golang which could create difficulties for users of some C libraries [here](https://docs.yottadb.com/Presentations/DragonsofCGO.pdf), especially where there are:
0. pointers to structs containing other pointers
1. callbacks
2. issues not apparent until garbage collection is triggered

### Performance

It is unclear whether the newer, faster firmware is supported on linux. From the manual:-

```
Pay attention : that newer firmware supports 2 interfaces:
1. HID -- it is universal and easy. Supported by all platforms. But it is slow
2. VCI -- available since firmware V2.10. On Windows requires a special driver (for
example zadig/Interface 1) It is faster. May be unavailable on Mac-OS
In this case both interfaces are listed as individual (separated\independent) items with
the same Serial Number.
It is bad idea to connect both interfaces at the same time and especially bad to perform
scan concurrently
```

Thus to use this newer firmware we will likely need to enumerate devices and handle lists, etc. This should be ok because the types in the C library can be used as parameters.

### Descriptions

Note that getting the first handle will literally just get a handle - you cannot access the description from that handle. If you want the description, you need to get a list of descriptions, and then hask for the handle for the description you like the best. So don't bother trying to access description fields from the handle or handle pointer.

#### Result codes

The result strings are copied from `pocket.h`, primarily to help with debugging by providing some meaning to non-zero error codes. The result from the functions is an C enum, which is only an `int`, so can be typecast back to Go int, then used as the index into an array of strings. For example, If there is no device, then attempting to get a device handle returns code 0x05, or `PVNA_Res_NoDevice` or if a function completes successfully it returns 0x00, which has the string `PVNA_Res_Ok`.

### Testing

The testing for this library assumes the presence of pocketVNA - this avoids mocking the API library and the hardware.

The testing routine issues are force unlock command which should unlock any available pocketVNA. Testing will take place with the first available handle found by the openAPI library. If there is no hardware available you will see:
```
=== RUN   TestGetReleaseHandle
    TestGetReleaseHandle: pocket_test.go:45: 
        	Error Trace:	pocket_test.go:45
        	Error:      	Received unexpected error:
        	            	PVNA_Res_NoDevice
        	Test:       	TestGetReleaseHandle
--- FAIL: TestGetReleaseHandle (0.00s)
```

This probably just means your pocketVNA is unplugged.

If you plug it in and it is working, then you will see the test(s) pass (this output before other tests were added)

```
go build -v && go test -v && go vet
=== RUN   TestGetReleaseHandle
--- PASS: TestGetReleaseHandle (0.06s)
PASS
ok  	_/home/your-path/go-pocketvna/pkg	0.100s
```

#### SingleQuery

Cable disconnected at port 1

```
=== RUN   TestSingleQuery
{(-3.302842378616333e-05-0.00019435584545135498i) (1.2695789337158203e-05-1.9058585166931152e-05i) (-7.614493370056152e-06-2.4139881134033203e-05i) (3.810226917266846e-05-0.00016132742166519165i)}
```

Cable connected

```
{(-0.0013300031423568726+0.000985749065876007i) (0.0026688948273658752-0.005279362201690674i) (0.002047717571258545-0.006369277834892273i) (-0.0012982413172721863+0.0008942857384681702i)}
```

### How to load a touchstone file in python

Install [scikit-rf](https://scikit-rf.readthedocs.io/en/latest/tutorials/Installation.html), usually
```
pip install scikit-rf

```

start a python session, load and plot your file (change to suit your filename)

```
import matplotlib.pyplot as plt
import skrf as rf
load = rf.Network('dut.s1p')
dut.plot_s_db()
plt.savefig('dut_db.png', dpi=300)
plt.close()
dut.plot_s_deg()
plt.savefig('dut_deg.png', dpi=300)
plt.close()
```

### API to the API

since pointers container pointers are difficult to handle, the preferred API is the range API, probably.

## Testability, and future substitution of other hardware ...

There is really only three commands that the user interface needs to know about - GetReasonableFrequencyRange, SingleQuery, RangeQuery.

Therefore a simple remote driver would grab a device handle, and sit back and wait for these commands.

Getting the callback to work would be pretty useful, too, for the rangequery command. Can we poke percentage complete values into a channel?

### Small gotchas with cgo

#### Could not determine type of name error

```
To access a struct, union, or enum type directly, prefix it with struct_, union_, or enum_, as in C.struct_stat.
```
for example
```
C.enum_PocketVNADistribution(distr), //note we have to add enum_ to access this name
```

### Preparing PI image

Use [pishrink](https://github.com/Drewsif/PiShrink)

```
sudo dd if=/dev/sdb of=/home/<user>/rpi-config/vna-cal-2022-01-31.img bs=4M status=progress
sudo pishrink.sh -p vna-cal-2022-01-31.img vna-cal-2022-01-31-shrunk.img
```

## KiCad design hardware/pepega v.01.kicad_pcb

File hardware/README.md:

The files in this subdirectory were supplied by Maksim Kuznetcov

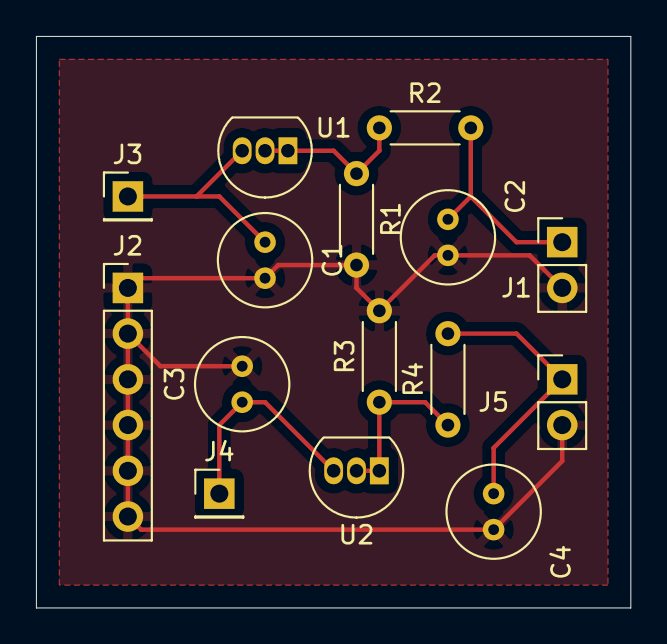
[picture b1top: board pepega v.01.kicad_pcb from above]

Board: 2 copper layers, 33.0 x 31.8 mm, 15 parts (0 on the bottom side), 7 nets.

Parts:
C1, C3: 0.1 uf; C_Radial_D5.0mm_H5.0mm_P2.00mm
C2, C4: 1 uf; C_Radial_D5.0mm_H5.0mm_P2.00mm
J1, J5: Conn_01x02; PinHeader_1x02_P2.54mm_Vertical
J2: Conn_01x06_Male; PinHeader_1x06_P2.54mm_Vertical
J3, J4: Conn_01x01_Male; PinHeader_1x01_P2.54mm_Vertical
R1, R3: 100; R_Axial_DIN0204_L3.6mm_D1.6mm_P5.08mm_Horizontal
R2, R4: 470; R_Axial_DIN0204_L3.6mm_D1.6mm_P5.08mm_Horizontal
U1, U2: LM317L_TO92; TO-92_Inline

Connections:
+5F: C3.1, J4.1, U2.3
+5V: C1.1, J3.1, U1.3
GND: C1.2, C2.2, C3.2, C4.2, J1.2, J2.1, J2.2, J2.3, J2.4, J2.5, J2.6, J5.2, R1.2, R3.2
unnamed: C2.1, J1.1, R2.2
unnamed: C4.1, J5.1, R4.2
unnamed: R1.1, R2.1, U1.1, U1.2
unnamed: R3.1, R4.1, U2.1, U2.2

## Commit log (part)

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2021-10-05 Initial commit from cgo-play/vna
2021-10-05 Re-arrange into a package
2021-10-05 Redo result handling
2021-10-05 Add info on testing to README
2021-10-05 Add stub for getting device info
2021-10-05 Add GetReasonableFrequencyRange
2021-10-05 Fix SParam construction in SingleQuery
2021-10-06 Add RangeQuery
2021-10-06 Move pocket to pkg/pocket
2021-10-12 Mods in progress
2021-10-15 Refactor for methods
2021-10-15 Add TestRun
2021-10-15 Add Queries to TestRun
2021-10-18 Add stream_test.go
2021-10-18 Change representation of complex to suit JSON encoder
2021-10-18 Improve TestPipeInterfaceToWs
2021-10-18 Add all commands to TestPipeWsToInterface
2021-10-18 Add rr to pkg/stream/TestRun
2021-10-18 Initialise /cmd
2021-10-18 Update package name for /cmd
2021-10-18 Fix cmd package name
2021-10-18 Add cmd/vna
2021-10-18 Implement cmd/vna stream command
2021-10-20 Add libraries to /lib
2021-10-20 Add heartbeat
2021-10-20 Add frequency to sq, rq results in pkg/pocket
2021-10-20 Add architecture support for amd64,arm
2021-10-20 Add images to README.md
2021-10-20 Add heartbeat to README.md
2021-10-26 Add rq example data
2022-01-20 Add cal demo
2022-01-20 Add tests in json.py
2022-01-20 Fix nan handling in clean_oneport
2022-01-20 Tidy imports in json.py
2022-01-20 Fix network_to_result for JSON serialisation
2022-01-20 Fix conversion to array in clean_oneport
2022-01-21 Move py test output images to ./img
2022-01-21 Add docker
2022-01-25 Extract arduino code
2022-01-25 Add new version of firmware
2022-01-25 Fix state assignment
2022-01-25 arduino: fix #defines/enum for switch
2022-01-25 Shift old Run to RunNoCal
2022-01-25 Add pkg/calibration
2022-01-25 Add tests to pkg/calibration
2022-01-25 Add TestMakeOnePort
2022-01-26 Add pkg/rfswitch
2022-01-26 Add SwitchMock to pkg/rfswitch test
2022-01-26 Add pkg/calibration/calibration
2022-01-26 Add TestPipeInterfaceToWs to calibration_test
2022-01-26 Add TestPipeWsToInterface to calibration_test
2022-01-26 Lowercase JSON keys in stream
2022-01-26 Add TestNew to pkg/stream
2022-01-26 Lowercase json keys in pkg/pocket structs
2022-01-26 Fix piping in pkg/stream/stream's New()
2022-01-26 Add cqr to TestNew in pkg/stream
2022-01-27 Add VNAService to pkg/pocket
2022-01-27 Change NewService to New in pkg/pocket
2022-01-27 Add pkg/middle
2022-01-27 Add pkg/drain to help with testing
2022-01-27 Fix Next() in pkg/drain
2022-01-27 Add TestMiddle to pkg/middle
2022-01-27 Refactor HandleRequest in pkg/middle
2022-01-27 Testing pkg/middle before refactor to use local session
2022-01-27 Add scan to struct pkg/calibration
2022-01-27 Add calibration to pkg/middle
2022-01-27 Add test for crq before rc pkg/middle
2022-01-27 Issue: Intermittent extra mds.Next() in middle_test
2022-01-27 Convert printf to log in pkg/middle
2022-01-28 Repeat setX x1000 in pkg/rfswitch/request_test
2022-01-28 Change cmd/vna to use middle
2022-01-28 Add validate.py script
2022-01-28 Add buildtools to Dockerfile
2022-01-28 Update documentation
2022-01-30 Update docker and ansible
2022-01-30 Fix rfswitch test
2022-01-31 Update README with pishrink
2022-02-01 Fix RFswitch message handling
    The arduino code sends blank lines occasionally, and the original
    rfswitch package was interpreting these as failed attempts at setting
    the port, causing calibration to fail. Since messages then got out of
    sequence, one blank line would cause subsequent responses to be out of
    sequence. Fixed by ignoring up to five unexpected messages after sending
    any command to the arduino, but still paying attention to whether any
2022-02-04 Add load touchstone to README
2022-02-04 Fix typo in heading/README.md
2022-02-24 fix(rfswitch):add logging to request
2022-02-24 fix(request): add more logging
2022-02-24 fix(middle): add logging
2022-02-24 Add lib files to pkg/pocket
2022-11-10 docs(add): new docs for two port
2022-11-10 arduino(feat): add support for two ports
2022-11-10 doc(feat): add two-port cal info
2022-11-10 calibration.py(feat): add two port wip
2022-11-10 py(fix): fix twelveterm inputs
2022-11-10 py(fix): two-port cal demo
2022-11-10 py(feat): write twoport.json
2022-11-10 py(feat): add S11,S22 correction
2022-11-10 py(fix): two port correction test
2022-11-10 py(feat): add twoport to client
2022-11-11 docker(fix): upgrade linux-amd64 to twoport
2022-11-11 py(fix): url setting in client
2022-11-11 pkg(wip): calibration
2022-11-15 doc(chore): reorganise into subject folders
2022-11-15 py(chore): put test data in separate dirs
2022-11-15 py(feat): add prepare-twoport-dataset wip
2022-11-17 py(feat): add twoport-dataset-2
    This dataset has good cal measurements and good result, and shows how the data
    should be loaded into the TwelveTerm cal object. Repeat for
    short/load/open: S11 result for the
    reflective standard on port one becomes S11, S11 result for port two
    becomes S22 in a two-port S-param set that has S12, S21 set to zero.
    It's not clear that the S11, S22 three-term Cal substitution needs to be
2022-11-17 py(fix): twoport-dataset-2 checks in calibration.py
2022-11-17 py(fix) remove 3t reflective cal
    The 3t cal for S11 and S22 produces worse results with dataset-2 so
    remove this hybridised-method until proven it is needed.
2022-11-17 calibration(fix): tests for twoport
2022-11-17 pkg(wip): twoport upgrade
2022-11-17 pkg(wip): checked pocket, stream tests work with hardware
2022-11-22 py(fix): validate wip
2022-11-22 arduino(fix): port number off by one
2022-11-22 chore: ignore cmd/vna/vna
2022-11-24 fix(middle): crq/rq select wip
2022-11-24 validate(fix): ready to diagnose switch issue
2022-11-25 arduino(fix): report pins in ascending order
2022-11-25 arduino(fix): turn off debug mode
2022-11-25 validate(chore): results to course team for checking
2023-02-28 py/validate (feat): add post_process
2023-02-28 py/validate (fix): titles on figs
2023-02-28 gitignore (chore): ignore zip files in doc
2023-02-28 all (chore): remove stale files
2023-02-28 py (fix): update docker README
2023-02-28 py (feat): add docker-login.sh
2023-02-28 sbc (fix): refactor scripts
2023-02-28 cmd (fix): include go.mod/sum
2023-02-28 sbc (fix): playbooks 05-08
2023-03-01 README (fix): add example commands
2023-03-03 README (fix): update port connections
2023-03-07 sbc (fix): updated playbooks
2023-03-23 validate (test): shows repeat measurement error
2023-03-23 py (fix): add repeats to validate
2023-03-23 pocket (fix): add hardware flag for tests
2023-03-23 pocket (chore): refactor common code
2023-03-23 pocket (feat): add Mock
2023-03-23 stream (fix): update for new VNA
2023-03-23 rfusb (feat): add direct serial for switch
2023-03-23 rfusb (feat): add mock
2023-03-31 py (feat): add calibrate.proto
2023-03-31 py (feat): test protoc server
    gRPC server implemented for two port calibration, and tested with python
    client using data from CopperMountainVNA - using calibrated data, and
    checking that the results are the same before and after calibration
    (because the error correction will be basically zero). Does not protect
    against an echo server implementation passing test, but for now we don't
    have a ready-made dataset with the raw DUT values to use.
2023-11-28 pkg (fix): update internal imports
2023-11-28 pkg/rfusb (fix): auto handle no hardware for test
2023-11-28 pkg/calibrate (feat): add test
2023-12-01 pkg/ptr (feat): demo interface with ptr receiver
2023-12-01 pkg/measure (fix): interface pointers
2023-12-01 pkg/measure (feat): add sq, frf methods
2023-12-01 pkg/pocket (fix): add what to sq
2023-12-01 README.md (fix): add diagram of cal meas
2023-12-01 pkg/stream (chore): update docstring
2023-12-01 go.mod (fix): update deps
2023-12-01 pkg/middle (fix): add timeout to test
2023-12-01 pkg/rfusb (fix): finish reads
2023-12-01 pkg/middle (fix): restructure rq
2023-12-01 pkg/middle (feat): handle crq
2023-12-01 pkg/middle (chore): remove stale code
2023-12-01 pkg/calibration (chore): remove this stale package
2023-12-01 cmd (fix): update for new middle
2023-12-01 build.sh (fix): buildtime
2023-12-01 pkg/middle (fix): add S12,S12,S22 to results
2023-12-01 cmd/stream (fix): export doc string
2023-12-06 2 port graphical copied from 1 port
2023-12-07 graphical input functions completed, still need images and testing and output values on different charts
2023-12-07 output graphs added for each s parameter
2023-12-11 updated to have ports that can be synced for the calibration and new placeholder command ready for firmware update for response when scanning
2023-12-13 have updated components to separate out the calibration parameters into a separate component. Next, need to add a new tab where the parameters are set
2023-12-15 py (fix): docker for odroid
2023-12-15 py (fix): add build.sh
2023-12-15 py (fix): +x docker scripts
2023-12-15 py (fix): README boot.ini for odroid
2023-12-15 py (fix): req grpc-1.0.0 -> grpcio-1.60.0
2023-12-15 py (fix): downgrade docker image to py3.7
2023-12-15 py (fix): upgrade to py3.12 & grpcio 1.60
2023-12-15 py (fix): rollback protobuf version
2023-12-15 pkg (fix): add arm64 (needs library)
2023-12-15 middle (feat): add stepwise calibration
2023-12-18 pkg (fix): arm64 lib name
2023-12-18 py (feat): add arm32 docker
2023-12-18 ui (fix): revert double measurement fix
2023-12-18 py (fix): add cmake in app-linux-arm32
2023-12-18 py/docker (fix): add gfortran to arm32 prereq
2023-12-20 sbc (fix): update files for grpc rollout
2023-12-20 sbc (feat): add install-on-odroid.sh
2023-12-20 py/docker (fix): pb2 and reqs
2023-12-20 sbc (fix): relay tokens via install-on-odroid
2023-12-20 py/docker (fix): add libopenblas for arm32
2023-12-20 sbc (fix): fw path
2023-12-20 sbc (fix): files.link in install-on-odroid.sh
2023-12-20 sbc (fix): enable relay.service install-on-odroid.sh
2023-12-20 sbc (fix): path for libPocketVnaApi install-on-odroid.sh
2023-12-20 sbc (fix): add docker to install-on-odroid.sh
2023-12-20 sbc (fix): install curl on odroid
2024-01-09 pocket (fix): add CalQuery
2024-01-09 middle (fix): add log for unknown command type
2024-01-09 pkg/pocket (fix): remove CalQuery
2024-01-09 pkg/middle (fix): remove CalQuery case from Handle()
2024-01-09 pkg (feat): add MCS to middle_test
2024-01-09 pkg (feat): step-wise cal test complete
2024-01-09 pkg (fix): populate what for cc response
2024-01-10 sc command and response updated
2024-01-10 commands working and data being received
2024-01-10 updated all hardware images
2024-01-10 2 port graphical UI complete and tested
2024-01-10 updated the min frequency in default UI too
2024-01-15 added env variables and appropriate base path for testing new dev server
2024-01-15 added default env base path
2024-01-15 base path added to router
2024-01-15 updated base path for images of cal standards
2024-01-15 returned id of pvna images to original format
2024-01-16 added an error modal and message if the calibration process is not complete
2024-01-16 added pvna id to navigation bar
2024-01-16 removing cal or dut now requires dragging out of area, not just click. Remains a click for touch screens
2024-01-16 removed test calibrate button
2024-01-16 ui(fix): minor issue with ID on table rows and ID of graphs clashing causing issue on drag and drop of components
2024-01-16 ui(fix): updated ID clash in default UI
2024-01-16 ui(feat): added pvna ID to navigation bar in default UI
2024-01-17 ui(fix): updated stringifying of query parameters in vue router so that the query is fully encoded as expected by the server
2024-01-17 removing the base property in createRouter as this is added in the createWebHistory function instead
2024-01-22 ui(update): minor changes to terminology used in UI and max data points set to 201
2024-01-22 ui(update): images of cal standards now have a short blue cable connected
2024-02-06 ui(update): minor update to DUT image size in ConnectAndDisplay component
2024-02-07 README(added): added a readme for the user interfaces
2024-03-20 ui (feat): add graphical ui dist
